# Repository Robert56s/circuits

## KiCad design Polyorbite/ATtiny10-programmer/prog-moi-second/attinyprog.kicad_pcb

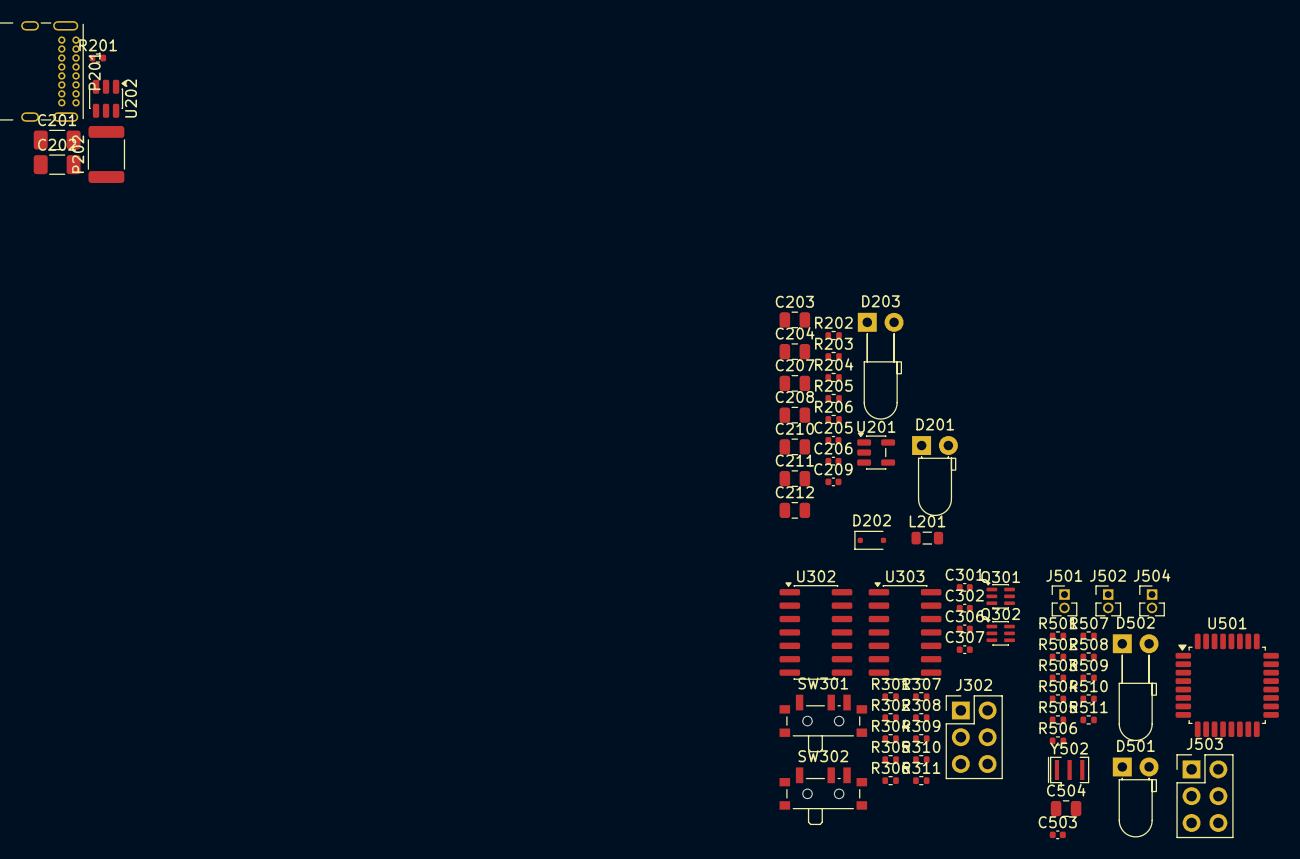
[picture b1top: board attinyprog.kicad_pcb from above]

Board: 2 copper layers, 68 parts (0 on the bottom side), 50 nets, no tracks yet.

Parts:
C201, C202: 1n@1kV; C_1206_3216Metric_Pad1.33x1.80mm_HandSolder
C203, C204, C207, C208, C210, C211, C212, C504: 10u; C_0805_2012Metric
C205, C206, C209, C301, C302, C306, C307, C503: 100n; C_0402_1005Metric
D201, D501: GREEN; LED_D3.0mm_Horizontal_O1.27mm_Z2.0mm
D202: BAT54J; D_SOD-323F
D203: GREEN; LED_D3.0mm_Horizontal_O3.81mm_Z6.0mm
D502: RED; LED_D3.0mm_Horizontal_O3.81mm_Z6.0mm
J302: Conn_02x03_Counter_Clockwise; PinHeader_2x03_P2.54mm_Vertical
J501: SELF PROGRAMMING; PinHeader_1x02_P1.27mm_Vertical
J502: SLOW SCK; PinHeader_1x02_P1.27mm_Vertical
J503: AVR-ISP-6; PinHeader_2x03_P2.54mm_Vertical
J504: UART; PinHeader_1x02_P1.27mm_Vertical
L201: 10u; L_0805_2012Metric
P201: USB_C_Plug_USB2.0; USB_C_Receptacle_GCT_USB4085
P202: 0ZCG0010FF2C; R_1812_4532Metric
Q301, Q302: MMDT2222A; SOT-363_SC-70-6
R201, R205, R206, R305, R307, R309, R311: 5.1k; R_0402_1005Metric
R202, R505, R506, R510, R511: 1k; R_0402_1005Metric
R203, R204, R301, R302, R304, R306, R308, R310, R501: 22k; R_0402_1005Metric
R502, R503, R504, R509: 270; R_0402_1005Metric
R507, R508: 68; R_0402_1005Metric
SW301, SW302: SW_SPDT; SW_SPDT_PCM12
U201: AP3012; SOT-23-5
U202: WE-TVS-82400102; SOT-23-6
U302, U303: CD4066BM; SO-14_3.9x8.65mm_P1.27mm
U501: ATmega88PB-A; TQFP-32_7x7mm_P0.8mm
Y502: 12MHz; Resonator_SMD_Murata_CSTxExxV-3Pin_3.0x1.1mm

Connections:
+5V: C203.1, C204.1, C205.1, C206.1, C210.1, C212.1, C503.1, C504.1, J503.2 (VCC), L201.1, P202.1, R202.1, R306.1, R310.1, R501.1, R505.2, R506.2, R511.1, SW301.2 (B), U201.4 (~SHDN), U201.5 (IN), U501.4 (VCC), U501.18 (AVCC)
+12V: C207.1, C208.1, C209.1, C211.1, C306.1, C307.1, D202.1 (K), R203.1, R206.1, R304.1, R308.1, SW302.1 (A), U302.14 (V_{DD}), U303.14 (V_{DD})
/arduino core/MISO: J503.1 (MISO), U501.16 (PB4)
/arduino core/RX: J504.1, U501.30 (PD0)
/arduino core/SLOW: J502.1, U501.25 (PC2)
/arduino core/TX: J504.2, R509.2
/arduino core/X+: U501.7 (XTAL1/PB6), Y502.1
/arduino core/X-: U501.8 (XTAL2/PB7), Y502.3
/arduino core/~RESET: J501.1, R501.2, U501.29 (~RESET/PC6)
/socket and selectors/ATTINY_{A}_VCC: C302.1, R301.1, R307.1, SW301.1 (A)
/socket and selectors/ATTINY_{B}_PB_{0}: J302.1, U303.2
/socket and selectors/ATTINY_{B}_PB_{1}: J302.3, U303.3
/socket and selectors/ATTINY_{B}_PB_{2}: J302.4, U303.9
/socket and selectors/ATTINY_{B}_VCC: C301.1, J302.5, R302.1, R311.1, SW301.3 (C)
/socket and selectors/ATTINY_{B}_~RESET: J302.6, U303.10
/socket and selectors/SWITCH_{A}: Q301.3 (C2), R304.2, U302.5, U302.6, U302.12, U302.13
/socket and selectors/SWITCH_{B}: Q302.3 (C2), R308.2, U303.5, U303.6, U303.12, U303.13
/socket and selectors/~RESET: SW302.2 (B), U302.11, U303.11
ATTINY_IN_PB_{0}: J503.4 (MOSI), R503.2, U302.1, U303.1
ATTINY_IN_PB_{1}: J503.3 (SCK), R504.2, U302.4, U303.4
ATTINY_IN_PB_{2}: U302.8, U303.8
ATTINY_IN_~RESET: J501.2, J503.5 (~RST), R502.2, SW302.3 (C)
D+: R508.2, U202.6
D-: R507.2, R510.2, U202.4
GND: C201.2, C202.2, C203.2, C204.2, C205.2, C206.2, C207.2, C208.2, C209.2, C210.2, C211.2, C212.2, C301.2, C302.2, C306.2, C307.2, C503.2, C504.2, D201.1 (K), D203.1 (K), J302.2, J502.2, J503.6 (GND), P201.A1 (GND), P201.A12 (GND), P201.B1 (GND), P201.B12 (GND), Q301.1 (E1), Q301.4 (E2), Q302.1 (E1), Q302.4 (E2), R201.2, R205.2, R301.2, R302.2, R305.1, R309.1, U201.2 (GND), U202.2, U302.7 (V_{SS}), U303.7 (V_{SS}), U501.5 (GND), U501.21 (GND), Y502.2
unnamed: D201.2 (A), R202.2
unnamed: D202.2 (A), L201.2, U201.1 (SW)
unnamed: D203.2 (A), R206.2
unnamed: D501.2 (A), R505.1
unnamed: D501.1 (K), U501.23 (PC0)
unnamed: D502.2 (A), R506.1
unnamed: D502.1 (K), U501.24 (PC1)
unnamed: P201.A5 (CC), R201.1
unnamed: P201.A6 (D+), U202.1
unnamed: P201.A7 (D-), U202.3
unnamed: C201.1, C202.1, P201.SH (SHIELD)
unnamed: Q301.2 (B1), R307.2
unnamed: Q301.5 (B2), Q301.6 (C1), R305.2, R306.2
unnamed: Q302.2 (B1), R311.2
unnamed: Q302.5 (B2), Q302.6 (C1), R309.2, R310.2
unnamed: R203.2, R204.1
unnamed: R510.1, R511.2
unnamed: R204.2, R205.1, U201.3 (FB)
unnamed: R507.1, U501.12 (PB0)
unnamed: R508.1, U501.13 (PB1), U501.32 (PD2)
unnamed: R502.1, U501.14 (PB2)
unnamed: R503.1, U501.15 (PB3)
unnamed: R504.1, U501.17 (PB5)
unnamed: R509.1, U501.31 (PD1)
VBUS: P201.A4 (VBUS), P201.A9 (VBUS), P201.B4 (VBUS), P201.B9 (VBUS), P202.2, U202.5

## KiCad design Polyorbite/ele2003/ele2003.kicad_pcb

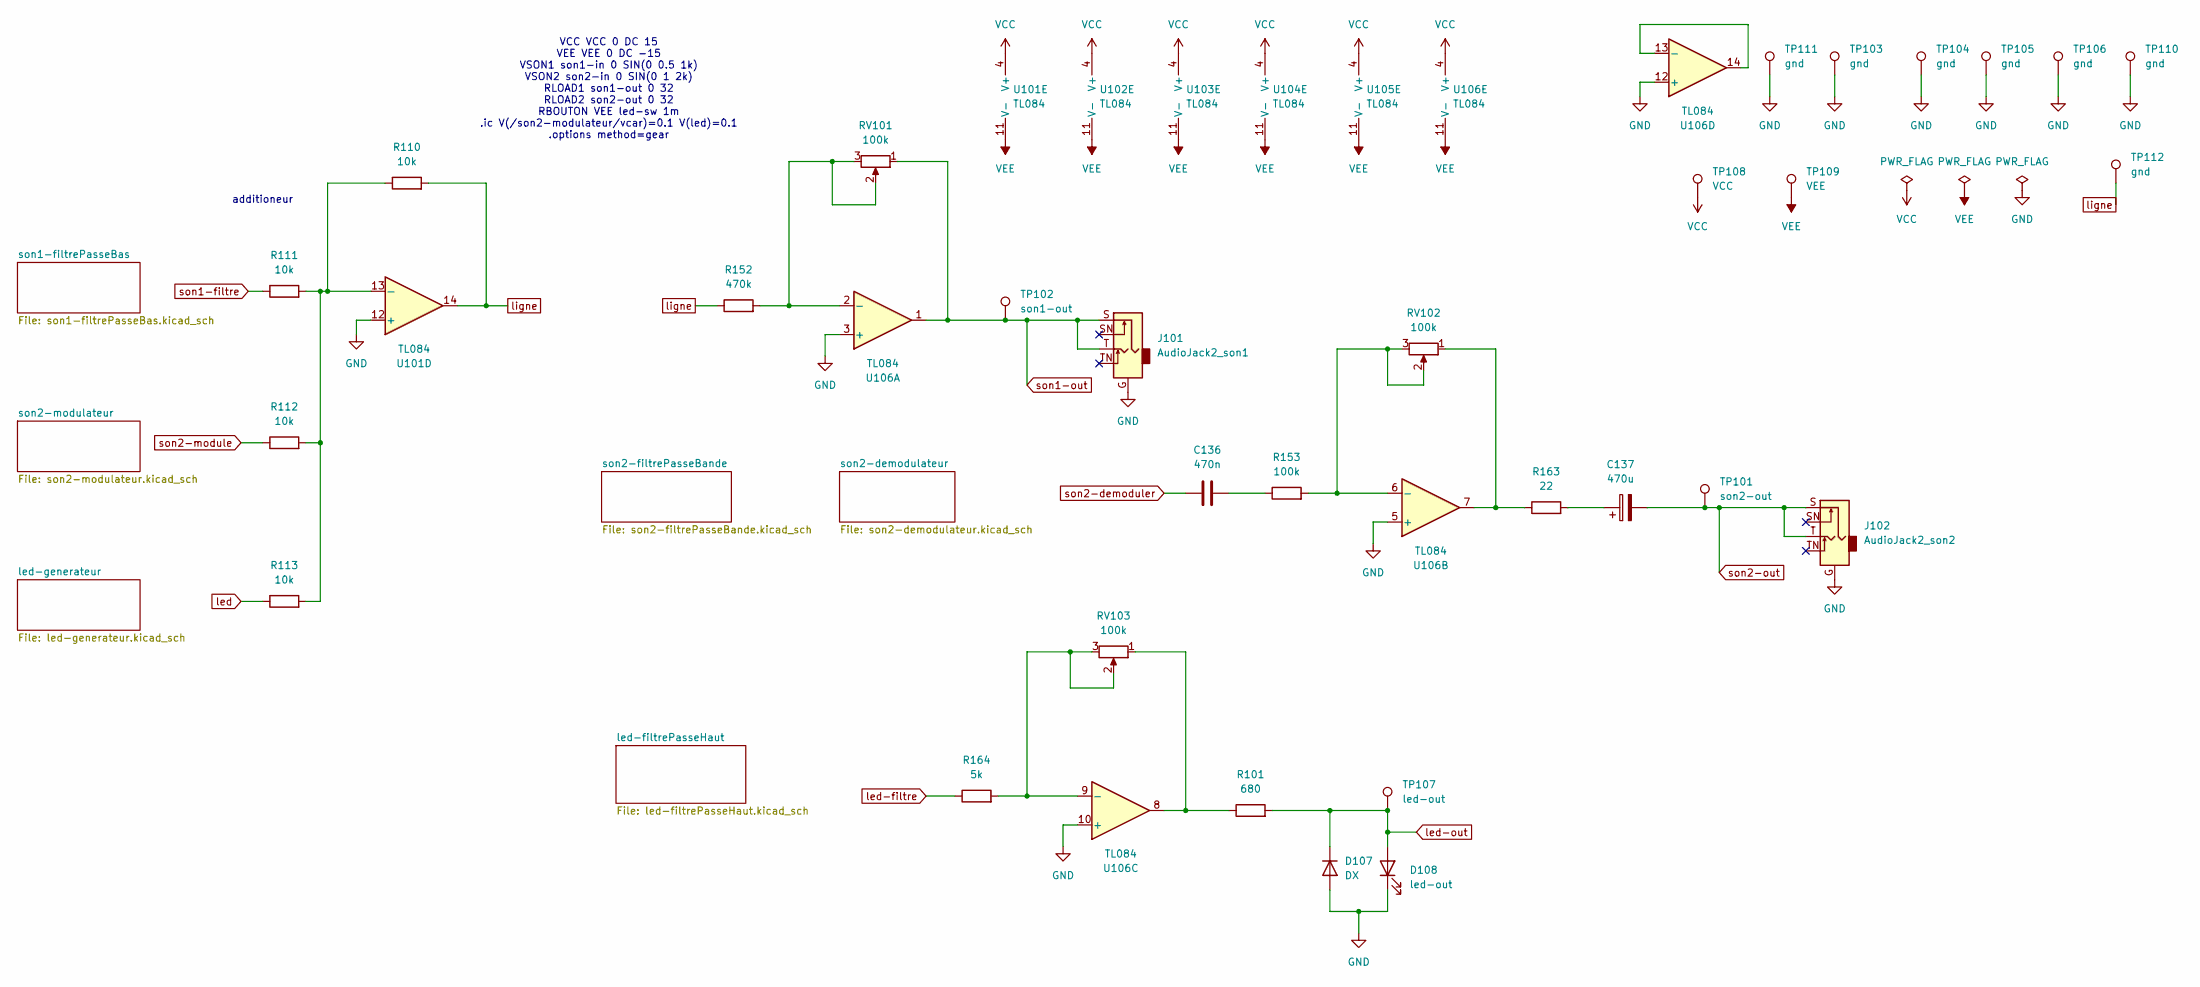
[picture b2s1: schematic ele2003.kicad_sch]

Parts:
C136: 470n; C_Disc_D4.3mm_W1.9mm_P5.00mm
C137: 470u; CP_Radial_D10.0mm_P5.00mm
D107: DX; D_DO-35_SOD27_P7.62mm_Horizontal
D108: led-out; LED_D5.0mm
J101: AudioJack2_son1; Jack_3.5mm_PJ-307_Horizontal
J102: AudioJack2_son2; Jack_3.5mm_PJ-307_Horizontal
R101: 680; R_Axial_DIN0207_L6.3mm_D2.5mm_P7.62mm_Horizontal
R110, R111, R112, R113: 10k; R_Axial_DIN0207_L6.3mm_D2.5mm_P7.62mm_Horizontal
R152: 470k; R_Axial_DIN0207_L6.3mm_D2.5mm_P7.62mm_Horizontal
R153: 100k; R_Axial_DIN0207_L6.3mm_D2.5mm_P7.62mm_Horizontal
R163: 22; R_Axial_DIN0207_L6.3mm_D2.5mm_P7.62mm_Horizontal
R164: 5k; R_Axial_DIN0207_L6.3mm_D2.5mm_P7.62mm_Horizontal
RV101, RV102, RV103: 100k; Potentiometer_Bourns_3362P_Vertical
TP101: son2-out; TestPoint_Bridge_Pitch5.08mm_Drill0.7mm
TP102: son1-out; TestPoint_Bridge_Pitch5.08mm_Drill0.7mm
TP103, TP104, TP105, TP106, TP110, TP111, TP112: gnd; TestPoint_Bridge_Pitch5.08mm_Drill0.7mm
TP107: led-out; TestPoint_Bridge_Pitch5.08mm_Drill0.7mm
TP108: VCC; TestPoint_Bridge_Pitch5.08mm_Drill0.7mm
TP109: VEE; TestPoint_Bridge_Pitch5.08mm_Drill0.7mm
U101, U102, U103, U104, U105, U106: TL084; DIP-14_W7.62mm

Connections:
GND: D107.2 (A), D108.1 (K), J101.G, J102.G, TP103.1 (1_1), TP104.1 (1_1), TP105.1 (1_1), TP106.1 (1_1), TP110.1 (1_1), TP111.1 (1_1), U101.12 (+), U106.3 (+), U106.5 (+), U106.10 (+), U106.12 (+); also elsewhere on the board
unnamed: C136.2, R153.1
unnamed: C137.1, R163.2
unnamed: R101.1, RV103.1, U106.8
unnamed: R163.1, RV102.1, U106.7
unnamed: R110.1, R111.2, R112.2, R113.2, U101.13 (-)
unnamed: R152.2, RV101.2, RV101.3, U106.2 (-)
unnamed: R153.2, RV102.2, RV102.3, U106.6 (-)
unnamed: R164.2, RV103.2, RV103.3, U106.9 (-)
unnamed: U106.13 (-), U106.14
VCC: TP108.1 (1_1), U101.4 (V+), U102.4 (V+), U103.4 (V+), U104.4 (V+), U105.4 (V+), U106.4 (V+); also elsewhere on the board
VEE: TP109.1 (1_1), U101.11 (V-), U102.11 (V-), U103.11 (V-), U104.11 (V-), U105.11 (V-), U106.11 (V-); also elsewhere on the board
led: R113.1; also elsewhere on the board
led-filtre: R164.1; also elsewhere on the board
led-out: D107.1 (K), D108.2 (A), R101.2, TP107.1 (1_1)
ligne: R110.2, R152.1, TP112.1 (1_1), U101.14; also elsewhere on the board
son1-filtre: R111.1; also elsewhere on the board
son1-out: J101.S, J101.T, RV101.1, TP102.1 (1_1), U106.1
son2-demoduler: C136.1; also elsewhere on the board
son2-module: R112.1; also elsewhere on the board
son2-out: C137.2, J102.S, J102.T, TP101.1 (1_1)

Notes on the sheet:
additioneur
VCC VCC 0 DC 15 VEE VEE 0 DC -15 VSON1 son1-in 0 SIN(0 0.5 1k) VSON2 son2-in 0 SIN(0 1 2k) RLOAD1 son1-out 0 32 RLOAD2 son2-out 0 32 RBOUTON VEE led-sw 1m .ic V(/son2-modulateur/vcar)=0.1 V(led)=0.1 .options method=gear

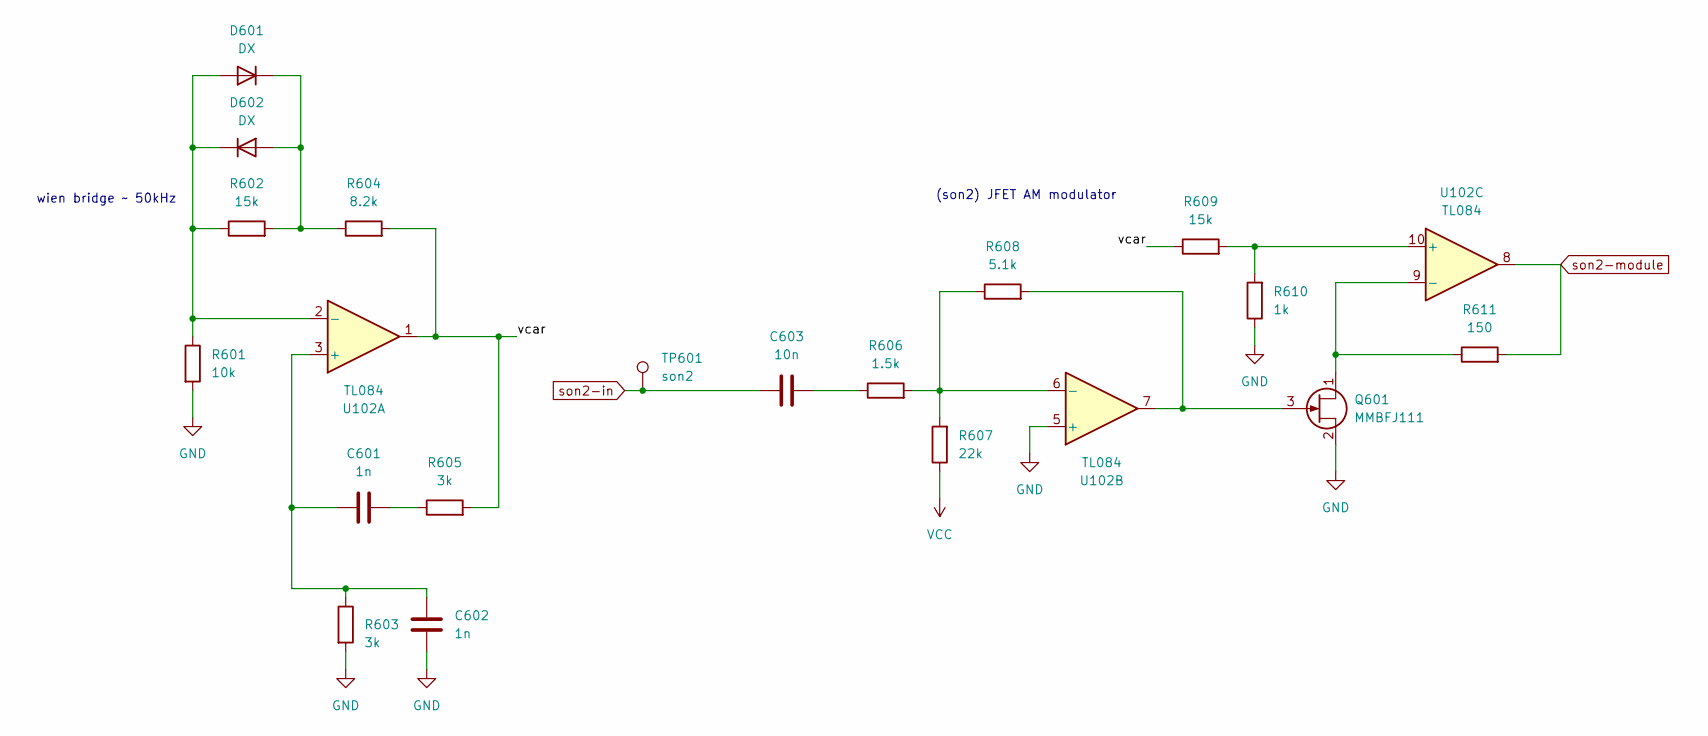
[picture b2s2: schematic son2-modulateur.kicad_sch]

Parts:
C601, C602: 1n; C_Disc_D4.3mm_W1.9mm_P5.00mm
C603: 10n; C_Disc_D4.3mm_W1.9mm_P5.00mm
D601, D602: DX; D_DO-35_SOD27_P7.62mm_Horizontal
Q601: MMBFJ111; TO-92_Inline
R601: 10k; R_Axial_DIN0207_L6.3mm_D2.5mm_P7.62mm_Horizontal
R602, R609: 15k; R_Axial_DIN0207_L6.3mm_D2.5mm_P7.62mm_Horizontal
R603, R605: 3k; R_Axial_DIN0207_L6.3mm_D2.5mm_P7.62mm_Horizontal
R604: 8.2k; R_Axial_DIN0207_L6.3mm_D2.5mm_P7.62mm_Horizontal
R606: 1.5k; R_Axial_DIN0207_L6.3mm_D2.5mm_P7.62mm_Horizontal
R607: 22k; R_Axial_DIN0207_L6.3mm_D2.5mm_P7.62mm_Horizontal
R608: 5.1k; R_Axial_DIN0207_L6.3mm_D2.5mm_P7.62mm_Horizontal
R610: 1k; R_Axial_DIN0207_L6.3mm_D2.5mm_P7.62mm_Horizontal
R611: 150; R_Axial_DIN0207_L6.3mm_D2.5mm_P7.62mm_Horizontal
TP601: son2; TestPoint_Bridge_Pitch5.08mm_Drill0.7mm
U102: TL084; DIP-14_W7.62mm

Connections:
/son2-modulateur/vcar: R604.2, R605.2, R609.1, U102.1
GND: C602.2, Q601.2 (S), R601.2, R603.2, R610.1, U102.5 (+); also elsewhere on the board
unnamed: C601.1, R605.1
unnamed: C603.2, R606.1
unnamed: D601.2 (A), D602.1 (K), R601.1, R602.1, U102.2 (-)
unnamed: D601.1 (K), D602.2 (A), R602.2, R604.1
unnamed: Q601.1 (D), R611.1, U102.9 (-)
unnamed: Q601.3 (G), R608.2, U102.7
unnamed: C601.2, C602.1, R603.1, U102.3 (+)
unnamed: R606.2, R607.2, R608.1, U102.6 (-)
unnamed: R609.2, R610.2, U102.10 (+)
VCC: R607.1; also elsewhere on the board
son2-in: C603.1, TP601.1 (1_1)
son2-module: R611.2, U102.8; also elsewhere on the board

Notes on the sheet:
wien bridge ~ 50kHz
(son2) JFET AM modulator

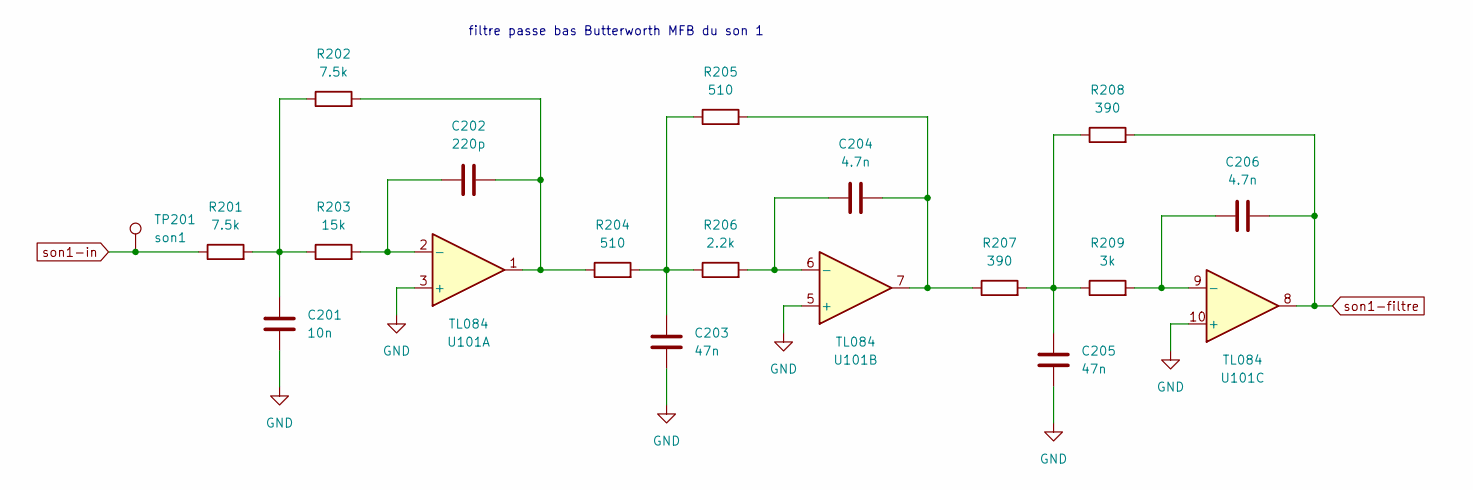
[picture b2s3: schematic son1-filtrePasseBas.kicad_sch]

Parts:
C201: 10n; C_Disc_D4.3mm_W1.9mm_P5.00mm
C202: 220p; C_Disc_D4.3mm_W1.9mm_P5.00mm
C203, C205: 47n; C_Disc_D4.3mm_W1.9mm_P5.00mm
C204, C206: 4.7n; C_Disc_D4.3mm_W1.9mm_P5.00mm
R201, R202: 7.5k; R_Axial_DIN0207_L6.3mm_D2.5mm_P7.62mm_Horizontal
R203: 15k; R_Axial_DIN0207_L6.3mm_D2.5mm_P7.62mm_Horizontal
R204, R205: 510; R_Axial_DIN0207_L6.3mm_D2.5mm_P7.62mm_Horizontal
R206: 2.2k; R_Axial_DIN0207_L6.3mm_D2.5mm_P7.62mm_Horizontal
R207, R208: 390; R_Axial_DIN0207_L6.3mm_D2.5mm_P7.62mm_Horizontal
R209: 3k; R_Axial_DIN0207_L6.3mm_D2.5mm_P7.62mm_Horizontal
TP201: son1; TestPoint_Bridge_Pitch5.08mm_Drill0.7mm
U101: TL084; DIP-14_W7.62mm

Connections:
GND: C201.1, C203.1, C205.1, U101.3 (+), U101.5 (+), U101.10 (+); also elsewhere on the board
unnamed: C201.2, R201.2, R202.1, R203.1
unnamed: C202.2, R202.2, R204.1, U101.1
unnamed: C203.2, R204.2, R205.1, R206.1
unnamed: C204.2, R205.2, R207.1, U101.7
unnamed: C205.2, R207.2, R208.1, R209.1
unnamed: C202.1, R203.2, U101.2 (-)
unnamed: C204.1, R206.2, U101.6 (-)
unnamed: C206.1, R209.2, U101.9 (-)
son1-filtre: C206.2, R208.2, U101.8; also elsewhere on the board
son1-in: R201.1, TP201.1 (1_1)

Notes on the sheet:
filtre passe bas Butterworth MFB du son 1

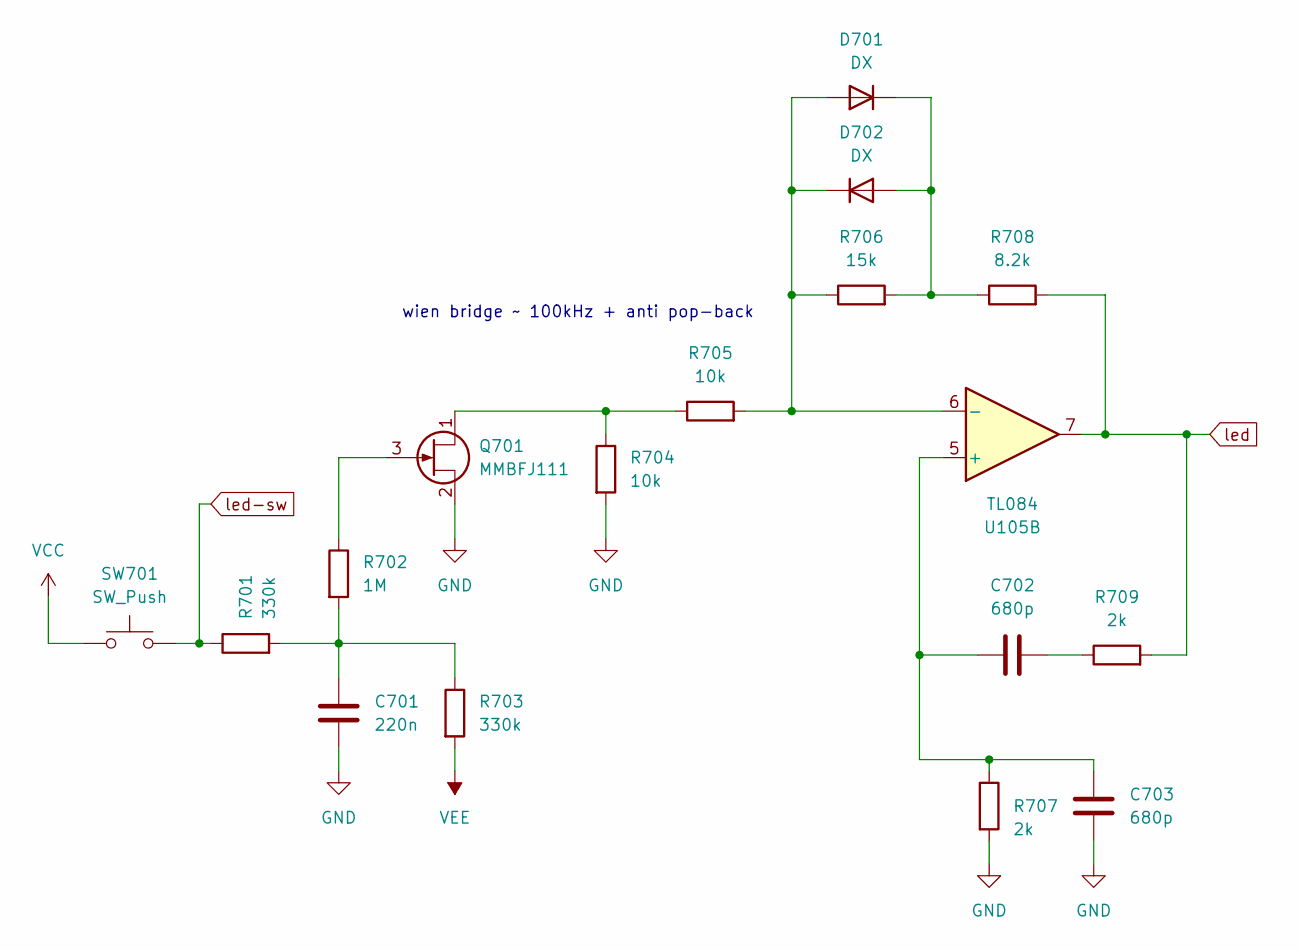
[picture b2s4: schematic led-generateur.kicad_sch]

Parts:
C701: 220n; C_Disc_D4.3mm_W1.9mm_P5.00mm
C702, C703: 680p; C_Disc_D4.3mm_W1.9mm_P5.00mm
D701, D702: DX; D_DO-35_SOD27_P7.62mm_Horizontal
Q701: MMBFJ111; TO-92_Inline
R701, R703: 330k; R_Axial_DIN0207_L6.3mm_D2.5mm_P7.62mm_Horizontal
R702: 1M; R_Axial_DIN0207_L6.3mm_D2.5mm_P7.62mm_Horizontal
R704, R705: 10k; R_Axial_DIN0207_L6.3mm_D2.5mm_P7.62mm_Horizontal
R706: 15k; R_Axial_DIN0207_L6.3mm_D2.5mm_P7.62mm_Horizontal
R707, R709: 2k; R_Axial_DIN0207_L6.3mm_D2.5mm_P7.62mm_Horizontal
R708: 8.2k; R_Axial_DIN0207_L6.3mm_D2.5mm_P7.62mm_Horizontal
SW701: SW_Push; SW_Tactile_6x6mm_2pin_P5.00mm
U105: TL084; DIP-14_W7.62mm

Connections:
GND: C701.2, C703.2, Q701.2 (S), R704.2, R707.2; also elsewhere on the board
unnamed: C701.1, R701.2, R702.2, R703.1
unnamed: C702.1, R709.1
unnamed: D701.2 (A), D702.1 (K), R705.2, R706.1, U105.6 (-)
unnamed: D701.1 (K), D702.2 (A), R706.2, R708.1
unnamed: Q701.1 (D), R704.1, R705.1
unnamed: Q701.3 (G), R702.1
unnamed: C702.2, C703.1, R707.1, U105.5 (+)
VCC: SW701.1; also elsewhere on the board
VEE: R703.2; also elsewhere on the board
led: R708.2, R709.2, U105.7; also elsewhere on the board
led-sw: R701.1, SW701.2

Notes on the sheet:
wien bridge ~ 100kHz + anti pop-back

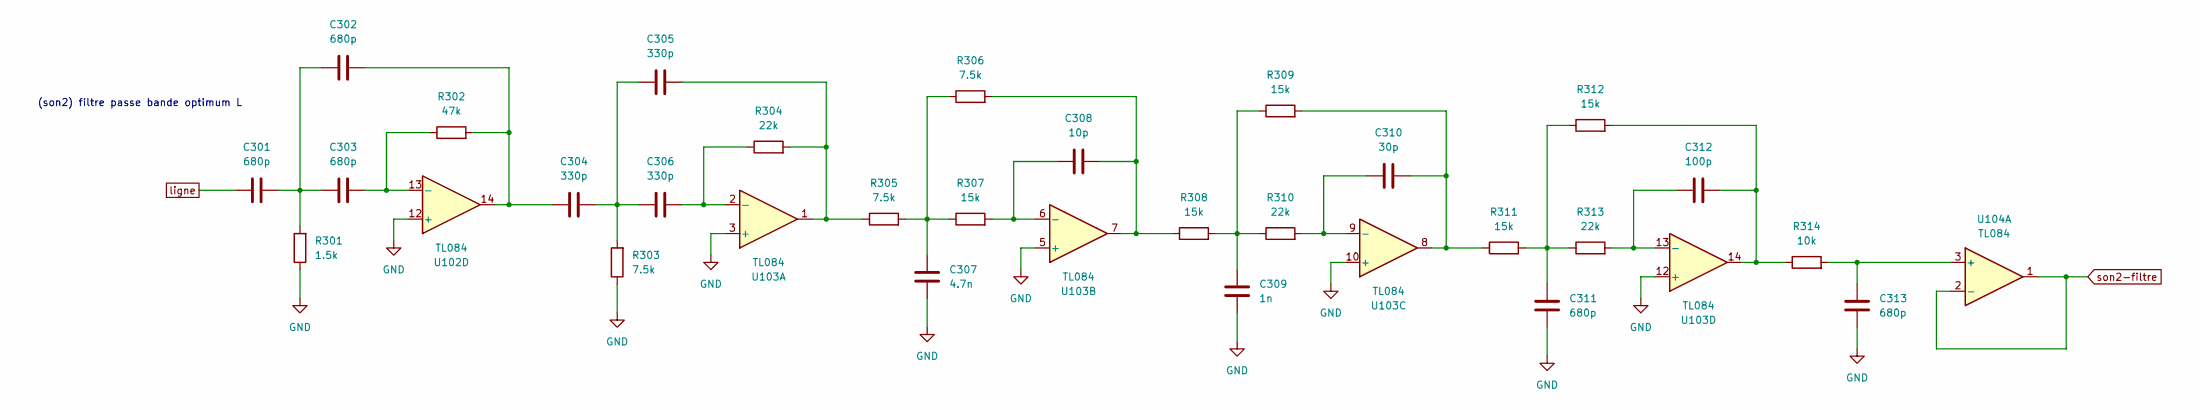
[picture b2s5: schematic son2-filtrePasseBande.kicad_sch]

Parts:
C301, C302, C303, C311, C313: 680p; C_Disc_D4.3mm_W1.9mm_P5.00mm
C304, C305, C306: 330p; C_Disc_D4.3mm_W1.9mm_P5.00mm
C307: 4.7n; C_Disc_D4.3mm_W1.9mm_P5.00mm
C308: 10p; C_Disc_D4.3mm_W1.9mm_P5.00mm
C309: 1n; C_Disc_D4.3mm_W1.9mm_P5.00mm
C310: 30p; C_Disc_D4.3mm_W1.9mm_P5.00mm
C312: 100p; C_Disc_D4.3mm_W1.9mm_P5.00mm
R301: 1.5k; R_Axial_DIN0207_L6.3mm_D2.5mm_P7.62mm_Horizontal
R302: 47k; R_Axial_DIN0207_L6.3mm_D2.5mm_P7.62mm_Horizontal
R303, R305, R306: 7.5k; R_Axial_DIN0207_L6.3mm_D2.5mm_P7.62mm_Horizontal
R304, R310, R313: 22k; R_Axial_DIN0207_L6.3mm_D2.5mm_P7.62mm_Horizontal
R307, R308, R309, R311, R312: 15k; R_Axial_DIN0207_L6.3mm_D2.5mm_P7.62mm_Horizontal
R314: 10k; R_Axial_DIN0207_L6.3mm_D2.5mm_P7.62mm_Horizontal
U102, U103, U104: TL084; DIP-14_W7.62mm

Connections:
GND: C307.1, C309.1, C311.1, C313.1, R301.1, R303.1, U102.12 (+), U103.3 (+), U103.5 (+), U103.10 (+), U103.12 (+); also elsewhere on the board
unnamed: C301.2, C302.1, C303.1, R301.2
unnamed: C302.2, C304.1, R302.2, U102.14
unnamed: C304.2, C305.1, C306.1, R303.2
unnamed: C305.2, R304.2, R305.1, U103.1
unnamed: C307.2, R305.2, R306.1, R307.1
unnamed: C308.2, R306.2, R308.1, U103.7
unnamed: C309.2, R308.2, R309.1, R310.1
unnamed: C310.2, R309.2, R311.1, U103.8
unnamed: C311.2, R311.2, R312.1, R313.1
unnamed: C312.2, R312.2, R314.1, U103.14
unnamed: C303.2, R302.1, U102.13 (-)
unnamed: C306.2, R304.1, U103.2 (-)
unnamed: C308.1, R307.2, U103.6 (-)
unnamed: C310.1, R310.2, U103.9 (-)
unnamed: C312.1, R313.2, U103.13 (-)
unnamed: C313.2, R314.2, U104.3 (+)
ligne: C301.1; also elsewhere on the board
son2-filtre: U104.1, U104.2 (-); also elsewhere on the board

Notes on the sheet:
(son2) filtre passe bande optimum L

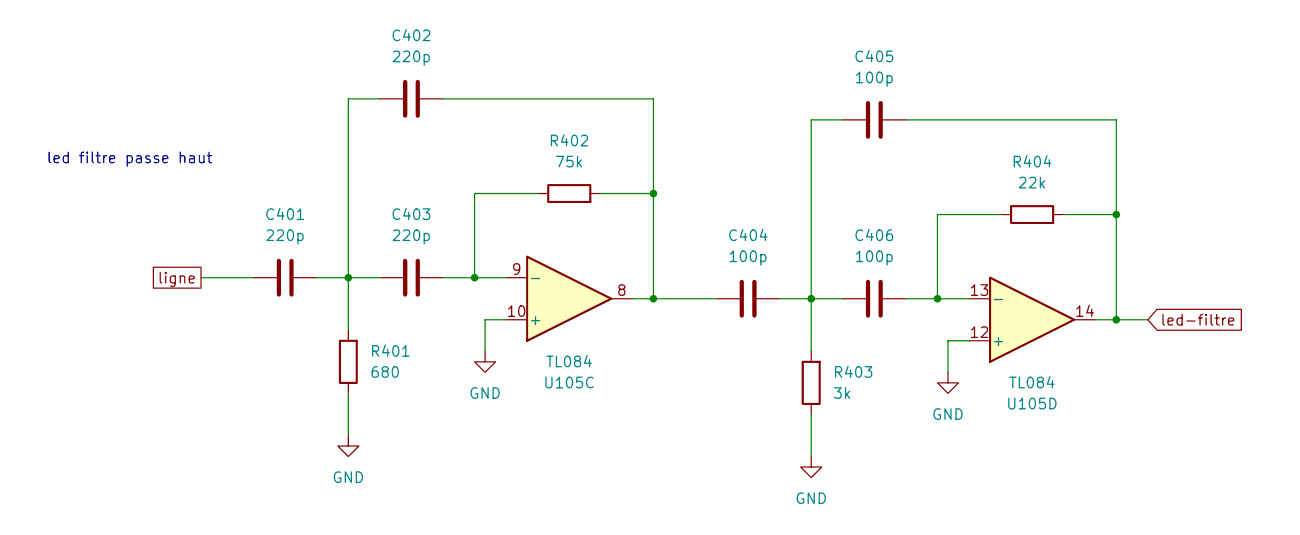
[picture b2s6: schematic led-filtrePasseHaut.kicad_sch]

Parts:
C401, C402, C403: 220p; C_Disc_D4.3mm_W1.9mm_P5.00mm
C404, C405, C406: 100p; C_Disc_D4.3mm_W1.9mm_P5.00mm
R401: 680; R_Axial_DIN0207_L6.3mm_D2.5mm_P7.62mm_Horizontal
R402: 75k; R_Axial_DIN0207_L6.3mm_D2.5mm_P7.62mm_Horizontal
R403: 3k; R_Axial_DIN0207_L6.3mm_D2.5mm_P7.62mm_Horizontal
R404: 22k; R_Axial_DIN0207_L6.3mm_D2.5mm_P7.62mm_Horizontal
U105: TL084; DIP-14_W7.62mm

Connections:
GND: R401.1, R403.1, U105.10 (+), U105.12 (+); also elsewhere on the board
unnamed: C401.2, C402.1, C403.1, R401.2
unnamed: C402.2, C404.1, R402.2, U105.8
unnamed: C404.2, C405.1, C406.1, R403.2
unnamed: C403.2, R402.1, U105.9 (-)
unnamed: C406.2, R404.1, U105.13 (-)
led-filtre: C405.2, R404.2, U105.14; also elsewhere on the board
ligne: C401.1; also elsewhere on the board

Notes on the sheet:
led filtre passe haut

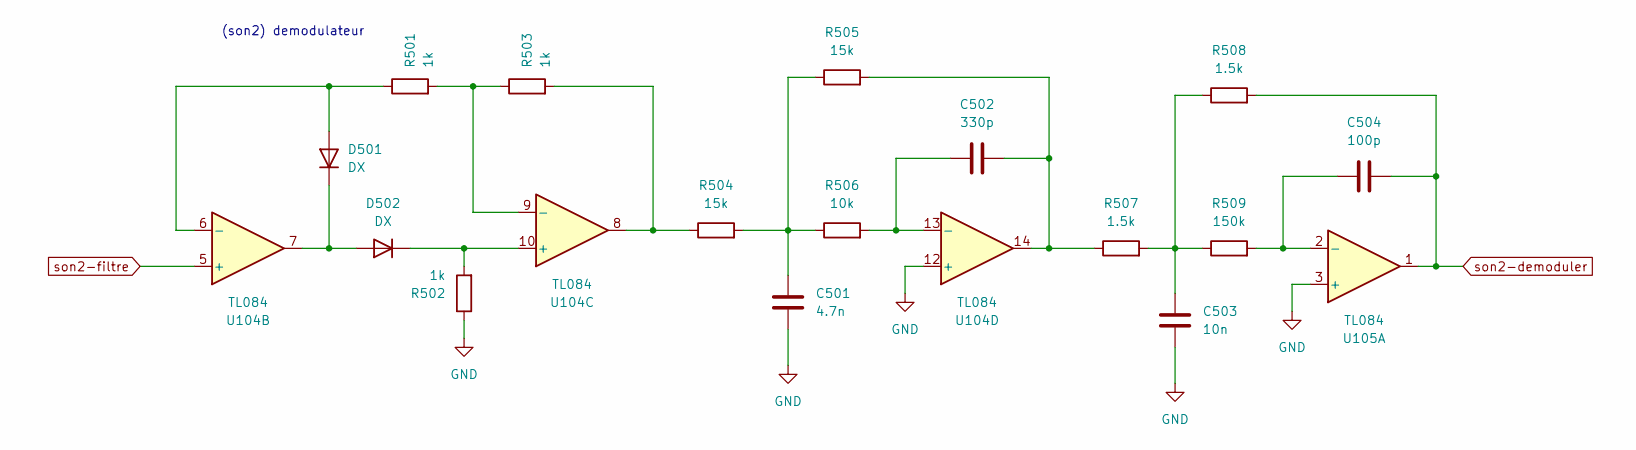
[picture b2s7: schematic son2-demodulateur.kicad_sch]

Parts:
C501: 4.7n; C_Disc_D4.3mm_W1.9mm_P5.00mm
C502: 330p; C_Disc_D4.3mm_W1.9mm_P5.00mm
C503: 10n; C_Disc_D4.3mm_W1.9mm_P5.00mm
C504: 100p; C_Disc_D4.3mm_W1.9mm_P5.00mm
D501, D502: DX; D_DO-35_SOD27_P7.62mm_Horizontal
R501, R502, R503: 1k; R_Axial_DIN0207_L6.3mm_D2.5mm_P7.62mm_Horizontal
R504, R505: 15k; R_Axial_DIN0207_L6.3mm_D2.5mm_P7.62mm_Horizontal
R506: 10k; R_Axial_DIN0207_L6.3mm_D2.5mm_P7.62mm_Horizontal
R507, R508: 1.5k; R_Axial_DIN0207_L6.3mm_D2.5mm_P7.62mm_Horizontal
R509: 150k; R_Axial_DIN0207_L6.3mm_D2.5mm_P7.62mm_Horizontal
U104, U105: TL084; DIP-14_W7.62mm

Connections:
GND: C501.1, C503.1, R502.1, U104.12 (+), U105.3 (+); also elsewhere on the board
unnamed: C501.2, R504.2, R505.1, R506.1
unnamed: C502.2, R505.2, R507.1, U104.14
unnamed: C503.2, R507.2, R508.1, R509.1
unnamed: D501.2 (A), R501.1, U104.6 (-)
unnamed: D501.1 (K), D502.2 (A), U104.7
unnamed: D502.1 (K), R502.2, U104.10 (+)
unnamed: R503.2, R504.1, U104.8
unnamed: R501.2, R503.1, U104.9 (-)
unnamed: C502.1, R506.2, U104.13 (-)
unnamed: C504.1, R509.2, U105.2 (-)
son2-demoduler: C504.2, R508.2, U105.1; also elsewhere on the board
son2-filtre: U104.5 (+); also elsewhere on the board

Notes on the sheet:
(son2) demodulateur

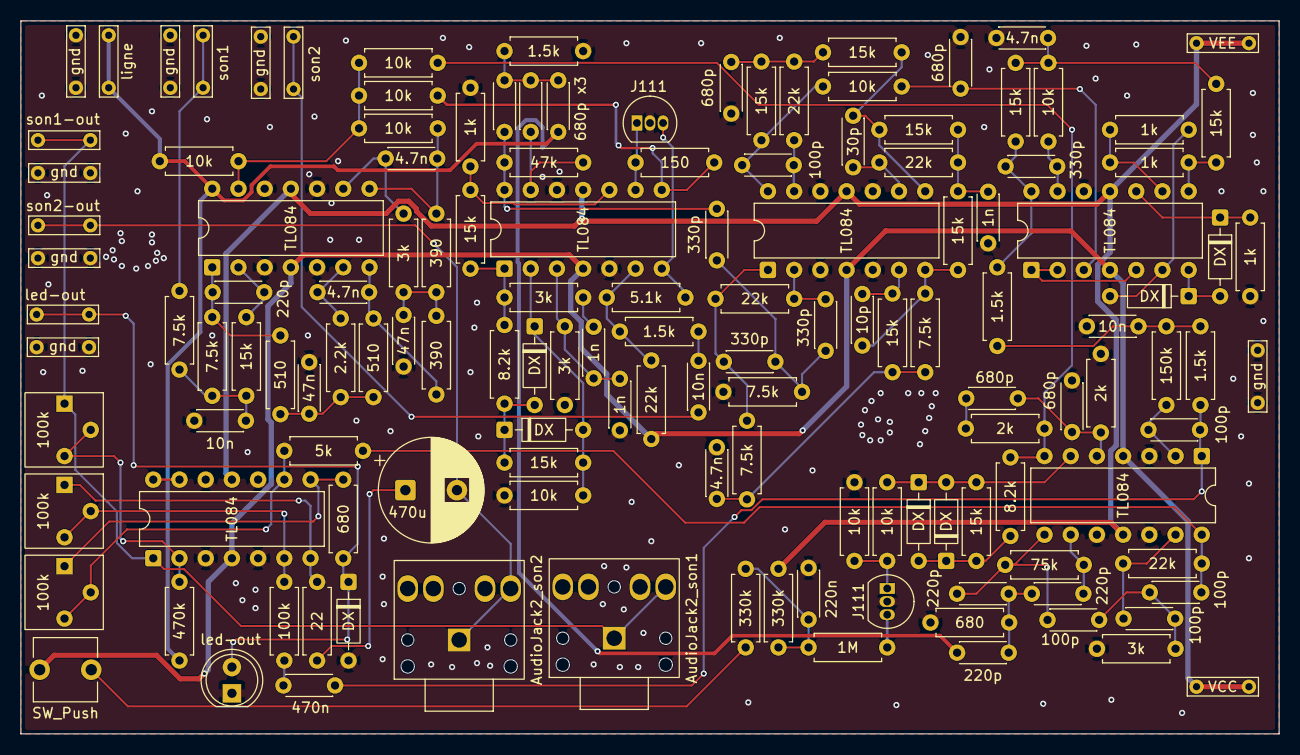
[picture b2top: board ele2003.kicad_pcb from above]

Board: 2 copper layers, 121.9 x 69.1 mm, 139 parts (0 on the bottom side), 81 nets.

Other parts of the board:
TP113: gnd; TestPoint_Bridge_Pitch5.08mm_Drill0.7mm

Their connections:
GND: TP113.1 (1_1); also elsewhere on the board

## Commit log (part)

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2025-11-03 circuit
2025-11-04 current
2025-11-07 fixed tp4
2025-11-07 cours8
2025-11-12 blabla
2025-11-13 update test arduino
2025-11-14 fuck you
2025-11-19 good
2025-11-19 push
